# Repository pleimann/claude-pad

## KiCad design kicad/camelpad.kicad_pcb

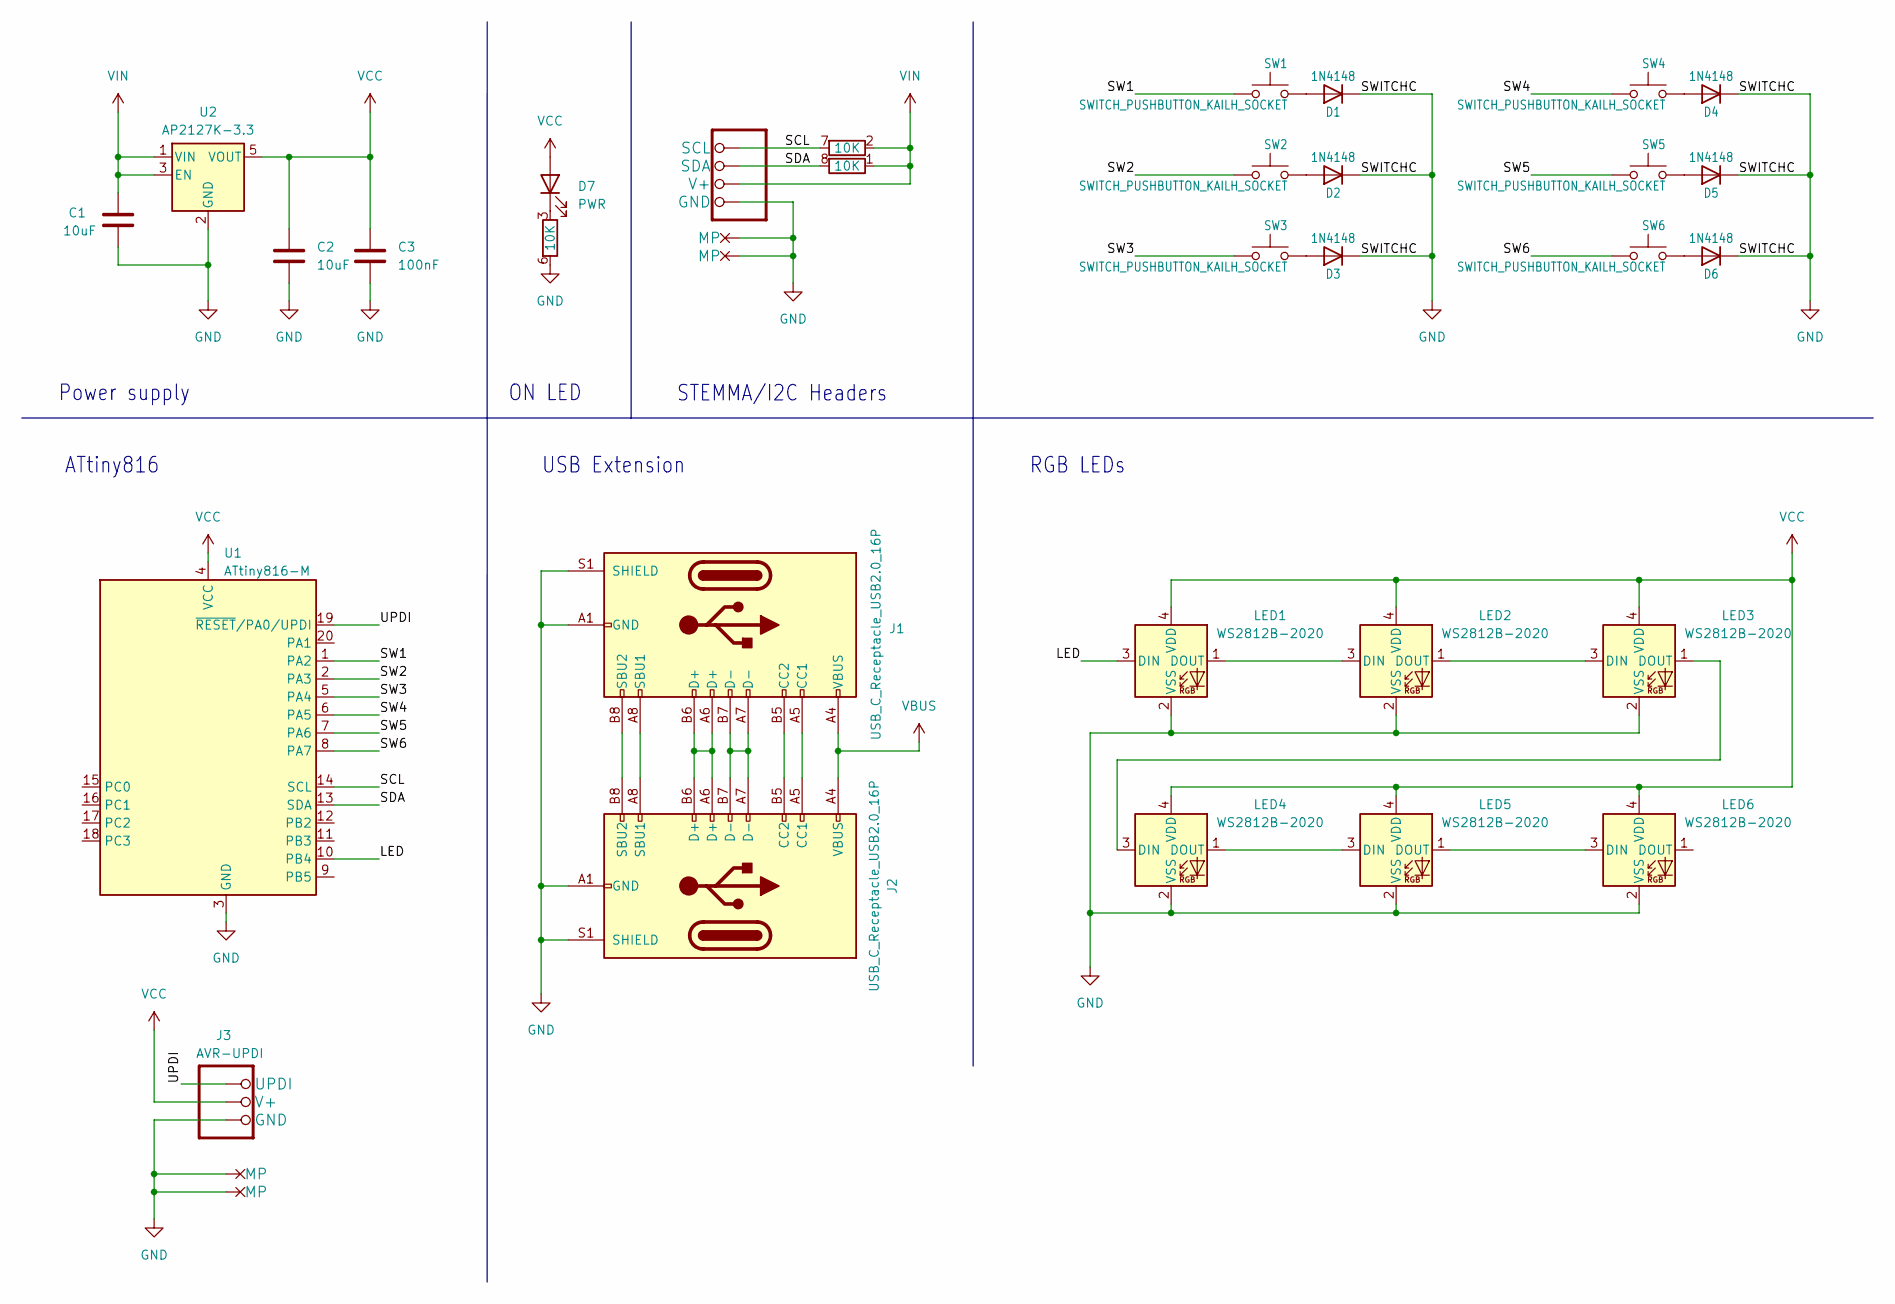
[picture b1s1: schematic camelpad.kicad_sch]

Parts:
C1, C2: 10uF; C_0603_1608Metric
C3: 100nF; C_0603_1608Metric
CONN1: JST_SH_BM04B-SRSS-TB_1x04-1MP_P1.00mm_Vertical
D1, D2, D3, D4, D5, D6: 1N4148; D_SOD-323
D7: PWR; LED_0402_1005Metric
J1: USB_C_Receptacle_USB2.0_16P; USB_C_Receptacle_Palconn_UTC16-G
J2: USB_C_Receptacle_USB2.0_16P; USB-C-SMD_GT-USB-7055E
J3: AVR-UPDI; JST_SH_BM04B-SRSS-TB_1x03-1MP_P1.00mm_Vertical
LED1, LED2, LED3, LED4, LED5, LED6: WS2812B-2020; LED-SMD_4P-L2.0-W2.0-TL_WS2812B-2020
RN1: 10K; R_Array_Convex_4x0603
SW1, SW2, SW3, SW4, SW5, SW6: SWITCH_PUSHBUTTON_KAILH_SOCKET; KAILH_SOCKET
U1: ATtiny816-M; VQFN-20-1EP_3x3mm_P0.4mm_EP1.7x1.7mm
U2: AP2127K-3.3; SOT-23-5

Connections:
/LED: LED1.3 (DIN), U1.10 (PB4)
/SCL: CONN1.4 (SCL), RN1.7 (R2.2), U1.14 (SCL)
/SDA: CONN1.3 (SDA), RN1.8 (R1.2), U1.13 (SDA)
/SW1: SW1.2, U1.1 (PA2)
/SW2: SW2.2, U1.2 (PA3)
/SW3: SW3.2, U1.5 (PA4)
/SW4: SW4.2, U1.6 (PA5)
/SW5: SW5.2, U1.7 (PA6)
/SW6: SW6.2, U1.8 (PA7)
/UPDI: J3.1 (UPDI), U1.19 (~RESET/PA0/UPDI)
GND: C1.1, C2.2, C3.2, CONN1.1 (GND), CONN1.5 (MP), CONN1.6 (MP), D1.1 (K), D2.1 (K), D3.1 (K), D4.1 (K), D5.1 (K), D6.1 (K), J1.A1 (GND), J1.A12 (GND), J1.B1 (GND), J1.B12 (GND), J1.S1 (SHIELD), J2.A1 (GND), J2.A12 (GND), J2.B1 (GND), J2.B12 (GND), J2.S1 (SHIELD), J3.3 (GND), J3.MP, LED1.2 (VSS), LED2.2 (VSS), LED3.2 (VSS), LED4.2 (VSS), LED5.2 (VSS), LED6.2 (VSS), RN1.6 (R3.2), U1.3 (GND), U2.2 (GND)
unnamed: D1.2 (A), SW1.1
unnamed: D2.2 (A), SW2.1
unnamed: D3.2 (A), SW3.1
unnamed: D4.2 (A), SW4.1
unnamed: D5.2 (A), SW5.1
unnamed: D6.2 (A), SW6.1
unnamed: D7.1 (K), RN1.3 (R3.1)
unnamed: J1.A5 (CC1), J2.A5 (CC1)
unnamed: J1.B5 (CC2), J2.B5 (CC2)
unnamed: J1.A6 (D+), J1.B6 (D+), J2.A6 (D+), J2.B6 (D+)
unnamed: J1.A7 (D-), J1.B7 (D-), J2.A7 (D-), J2.B7 (D-)
unnamed: J1.A8 (SBU1), J2.A8 (SBU1)
unnamed: J1.B8 (SBU2), J2.B8 (SBU2)
unnamed: LED1.1 (DOUT), LED2.3 (DIN)
unnamed: LED2.1 (DOUT), LED3.3 (DIN)
unnamed: LED3.1 (DOUT), LED4.3 (DIN)
unnamed: LED4.1 (DOUT), LED5.3 (DIN)
unnamed: LED5.1 (DOUT), LED6.3 (DIN)
VBUS: J1.A4 (VBUS), J1.A9 (VBUS), J1.B4 (VBUS), J1.B9 (VBUS), J2.A4 (VBUS), J2.A9 (VBUS), J2.B4 (VBUS), J2.B9 (VBUS)
VCC: C2.1, C3.1, D7.2 (A), J3.2 (V+), LED1.4 (VDD), LED2.4 (VDD), LED3.4 (VDD), LED4.4 (VDD), LED5.4 (VDD), LED6.4 (VDD), U1.4 (VCC), U2.5 (VOUT)
VIN: C1.2, CONN1.2 (V+), RN1.1 (R1.1), RN1.2 (R2.1), U2.1 (VIN), U2.3 (EN)

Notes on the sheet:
STEMMA/I2C Headers
Power supply
ON LED
RGB LEDs
USB Extension
ATtiny816

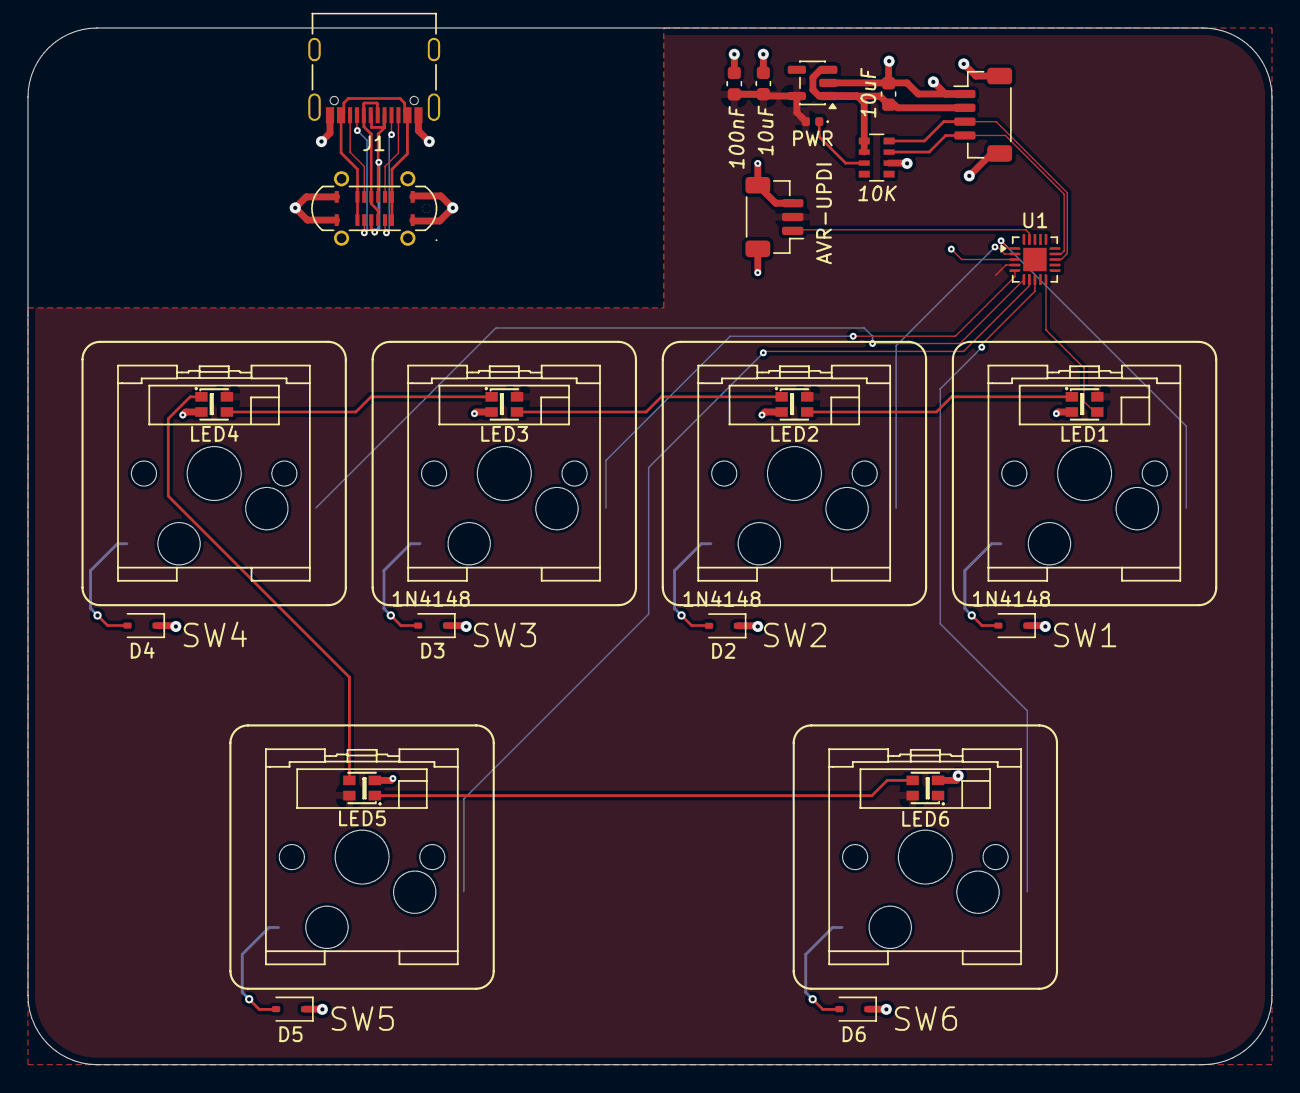
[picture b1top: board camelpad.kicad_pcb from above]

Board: 2 copper layers, 90.0 x 75.0 mm, 29 parts (0 on the bottom side), 32 nets.

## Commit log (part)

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2026-01-20 Add build and sync scripts
2026-01-21 reorganize files and rename package
2026-01-27 Simplify custom HID to use only 64-byte OUT report
    Remove Feature report (1024 bytes) and keep just the OUT report for
    host-to-device messaging. The 64-byte OUT report is simpler and sufficient
    for most use cases.
    - Report ID 2 is now the OUT report (was previously ID 3)
    - Removed Feature report handling from custom_hid.py and controller.py
    - Updated documentation to reflect simplified protocol
2026-01-30 display example
2026-01-31 update camel-pad
2026-01-31 ignore kicad dir for now
2026-02-01 Fix pad communications
2026-02-06 Add Seesaw component support and update configuration in esphome.yaml
2026-02-14 Bump cryptography in /firmware in the uv group across 1 directory
    Bumps the uv group with 1 update in the /firmware directory: [cryptography](https://github.com/pyca/cryptography).
    Updates `cryptography` from 46.0.4 to 46.0.5
    - [Changelog](https://github.com/pyca/cryptography/blob/main/CHANGELOG.rst)
    - [Commits](https://github.com/pyca/cryptography/compare/46.0.4...46.0.5)
    ---
    updated-dependencies:
2026-02-14 Bump cryptography from 46.0.4 to 46.0.5 in /firmware in the uv group across 1 directory (#3)
    Bumps the uv group with 1 update in the /firmware directory:
    [cryptography](https://github.com/pyca/cryptography).
    Updates `cryptography` from 46.0.4 to 46.0.5
    <details>
    <summary>Changelog</summary>
    <p><em>Sourced from <a
2026-02-17 config: add font size constants for UI elements
2026-02-17 display: increase notification label font to 28px
2026-02-24 firmware: ignore incompatible generic SD library
    PlatformIO's LDF was transitively pulling in the generic Arduino SD
    library (SPI-based, AVR-only) via the Adafruit seesaw dependency.
    That library's Sd2PinMap.h unconditionally errors on non-AVR targets.
    The firmware uses SD_MMC.h (ESP32-native SDMMC peripheral, part of the
    Arduino-ESP32 framework) and has no need for the generic SD library.
    Adding lib_ignore = SD prevents PlatformIO from compiling it.
2026-02-24 Fix keybindings form not loading snake_case gesture keys from config
    The YAML config uses double_press / long_press (snake_case) while the
    form was looking up doublePress / longPress (camelCase), leaving all
    gesture rows blank when opening the Keys tab.
    Add a snake fallback to each KB_GESTURES entry and update the mapping
    lookup in renderKeybindings to check both forms:
    keyMapping[g.id] || keyMapping[g.snake] || {}
2026-02-24 Fix Keys tab not loading current keybindings from config
    Two bugs prevented the form from showing existing keybinding data:
    1. populateForm() and renderKeybindings() shared a single try-catch block,
    so any error in populateForm() (e.g. unexpected config values) would
    silently swallow the exception and skip renderKeybindings entirely,
    leaving the Keys tab blank with no cards at all. Now each call has its
    own error boundary so renderKeybindings always runs after the config
2026-02-26 fix: add splash screen asset and clean up HTML formatting
